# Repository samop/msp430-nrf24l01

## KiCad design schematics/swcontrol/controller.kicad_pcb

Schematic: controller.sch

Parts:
C1: 100n; C_0805
C2: 1n; C_0805
P1: BK24x1; Pin_Header_Straight_2x04
P2: BSL; Pin_Header_Straight_1x07
P3: PWRBRD; Pin_Header_Straight_1x07
R1: 47k; R_0805
U1: MSP430F1222IDW; SSOP-28

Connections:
+3V3: C1.1, P1.7, P2.1, P3.5, R1.1, U1.2
GND: C1.2, C2.2, P1.8, P2.2, P3.1, U1.4
unnamed: C2.1, P2.4, R1.2, U1.7
unnamed: P1.2, U1.13
unnamed: P1.3, U1.12
unnamed: P1.4, U1.14
unnamed: P1.5, U1.18
unnamed: P1.6, U1.17
unnamed: P2.3, U1.1
unnamed: P2.5, P3.2, U1.22
unnamed: P2.6, U1.10
unnamed: P2.7, U1.25
unnamed: P3.3, U1.8
unnamed: P3.4, U1.24
unnamed: P3.6, U1.23
unnamed: P3.7, U1.21

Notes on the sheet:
Additional Triac Controls

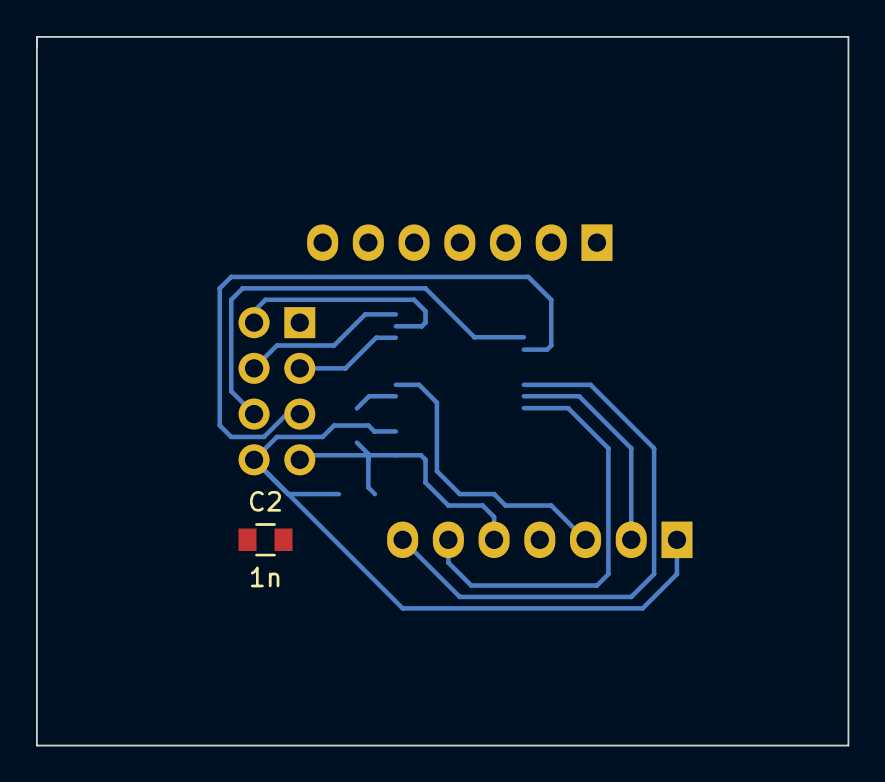
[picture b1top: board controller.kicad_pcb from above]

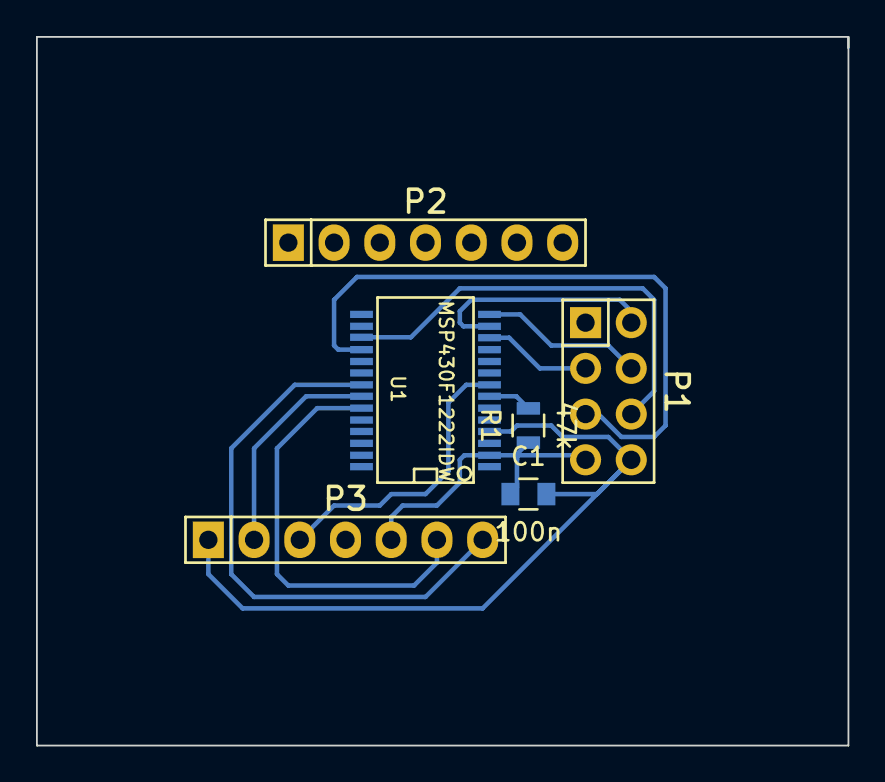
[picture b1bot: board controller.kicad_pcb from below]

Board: 2 copper layers, 45.1 x 39.4 mm, 7 parts (6 on the bottom side), 16 nets.

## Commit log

2014-02-12 Initial commit of init code
2014-02-13 Working code
2014-02-19 Prepared for fireing up at correct time
2015-01-10 Added program for wireless control of the prototype, broke ariginal program
2015-01-10 Addedd squarefortm generator for msp430g2211 (50hz)
2015-01-10 Working dimming (sending letter a or b through wireless)
2015-01-10 Simplified code; but found out it does not work, because of hardware null detect problem. Reprogramming in progress.
2015-01-11 On the test waveform it works perfectly, but in relaity it doesnt. I need to see the waveforms in the mains.
2015-02-03 Fixed a minot stupid bug.
2015-02-03 Added interrupt files...
2015-02-03 Working code. Receiving a,b,c
2015-03-01 Moved old code into separate diretory to avoid confusion
2015-03-01 Added webpage into the tree
2015-03-01 added missing files (maybe they must be removed)
2015-03-01 Added ARM code for transceiver
2015-03-01 Started schematics for controller fo the switch usign wrong uC
2015-03-01 Changing uC
2015-04-17 finished dimming program
2015-04-28 Added makefile and zero cross detect
2015-04-28 Fixed bugs, still not working correctly.
2015-05-03 Still not functional
2015-05-03 Added possibilities of transmitter to send any other code not just a b or c.
2015-05-04 Changed data structures and added softstartstop files. No soft start stop routines done yet.
2015-05-04 Soft start completed :D
2015-05-05 Fixed schematics
2015-05-05 Mini transceiver added on board
2015-05-05 Playing with PORT2 interrut. Still don't know why it doesnt work.
2015-05-05 Basic capsense
2015-05-05 Better touch
2015-05-05 Not working anymore :(
2015-05-05 Finalized button touch with timer A0
2015-05-09 added msp430g2533 code, but SPI does not work
2015-06-16 Trying to debug why the receiver does not work. I suspect the mix of the different transceivers, but i am not sure
2015-06-16 Great, it works with g2553 and nRF
2015-06-16 Reverted to the original controller code with new chip
